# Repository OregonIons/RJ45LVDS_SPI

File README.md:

# RJ45LVDS_SPI

Converts from 4x LVDS over ethernet cable (RJ45) to 4x single-ended digital on a 0.1" header.  
Small footprint board designed to be panel mounted inside a project case.  
Ideal for connecting remote SPI devices to the [Sinara hardware](https://github.com/m-labs/sinara) being designed for [ARTIQ](https://github.com/m-labs/artiq) (specifically the [RJ45_LVDS Kasli module](https://github.com/m-labs/sinara/wiki/EEM_RJ45_LVDS)).  
Voltage translation allows connection to 1.8, 2.5, 3.3, or 5V voltage node logic.

Power
=====

Board requires 3.3V (max current draw is ~200mA). Two options:

1. Apply regulated 3.3V power to the 3.3V pin on either header.  
or
2. Apply unregulated power to UNREG pin and enable the regulator by soldering REG_EN jumper.

- The default regulator is a MIC39100-3.3WS which requires an UNREG input voltage between 3.7 and 16V.  [Datasheet](http://ww1.microchip.com/downloads/en/DeviceDoc/mic39100.pdf)
- When applying unregulated power, the 3.3V pins on the two headers become outputs that can be used to power other things, such as an SPI device. The MIC39100-3.3WS is capable of providing 1A (minus the current required by the board). 
- Adding the optional resistor R5 makes the green LED on the RJ45 jack act as a power indicator.

Channel directions
==================

- Each channel can be independently configured as an input or an output.  
- The channel directions are set via the solder jumpers on the back of the board.  You must set all four directions before powering the board.  
- Each channel has two jumpers which must both be set the same way.

LVDS interface
==============

- Uses Texas Instruments SN65MLVD206 Line Driver and Receiver [Datasheet](http://www.ti.com/lit/ds/symlink/sn65mlvd206.pdf)
- Signalling rates up to 200 Mbps
- Driver has 1.5ns of propagation delay
- Receiver has 4ns of propagation delay

Single-ended digital interface
==============================

- Uses Texas Instruments SN74LVC1T45DBVR Bus Transceiver With Configurable Voltage Translation [Datasheet](http://http://www.ti.com/lit/ds/symlink/sn74lvc1t45.pdf)
- The voltage level of interface must be configured using one of the two V_LOGIC solder jumpers:
1. 3.3V - uses the board’s 3.3V rail
2. EXT - uses voltage supplied at V_LOGIC pin.  Must be in range 1.65-5.5V.
- EXT can be supplied at 'EXT V_LOGIC' pin or the 'UNREG to EXT V_LOGIC' jumper can be used to connect EXT to UNREG.  This would typically be done when powering the board from a regulated +5V supply.
- Propagation delays and data rates depend on V_LOGIC voltage level.  At 3.3V though they are ~4ns and 210Mbps.

RJ45 Connector
==============

Amphenol MRJ-5381-01. See [Datasheet](https://www.amphenolcanada.com/ProductSearch/drawings/AC/MRJ53xxx1.pdf) for panel cutout drawing.

Inverter
========

An optional inverter circuit is provided.  The inverter is an SC70-5 package and is supplied from V_LOGIC.  SN74LVC1GU04 [Datasheet](http://www.ti.com/lit/ds/symlink/sn74lvc1gu04.pdf) is the recommended part as it will work for all supported V_LOGIC voltages (1.8-5V).  Both input and output are wired to a 2-pin 0.1" header  The main envisaged use case is to produce an inverted CS line so that two SPI devices can be driven by the same board.

Release Notes
=============

v0.1 - Initial board fab run.

v0.2 - Second board fab run. Fixed some routing errors that made v0.1 untestable.  Board tested and working.

v0.3 - Changed the RJ45 connector to a right-angled panel-mount version.  Fixed a few silkscreen mistakes.

v0.4 - Fixed a slight error on RJ45 footprint.  Added 3.3V to logic header.  Used nicer solder jumpers.  Added third mounting hole.  Made room so power header could mount on top of board.  Added inverter circuit.

Things to fix in v1.0
=====================

- Inverter input and output labeled wrong on silkscreen.
- Make production files for boardhouse

Licence
=======

Zero-Clause BSD

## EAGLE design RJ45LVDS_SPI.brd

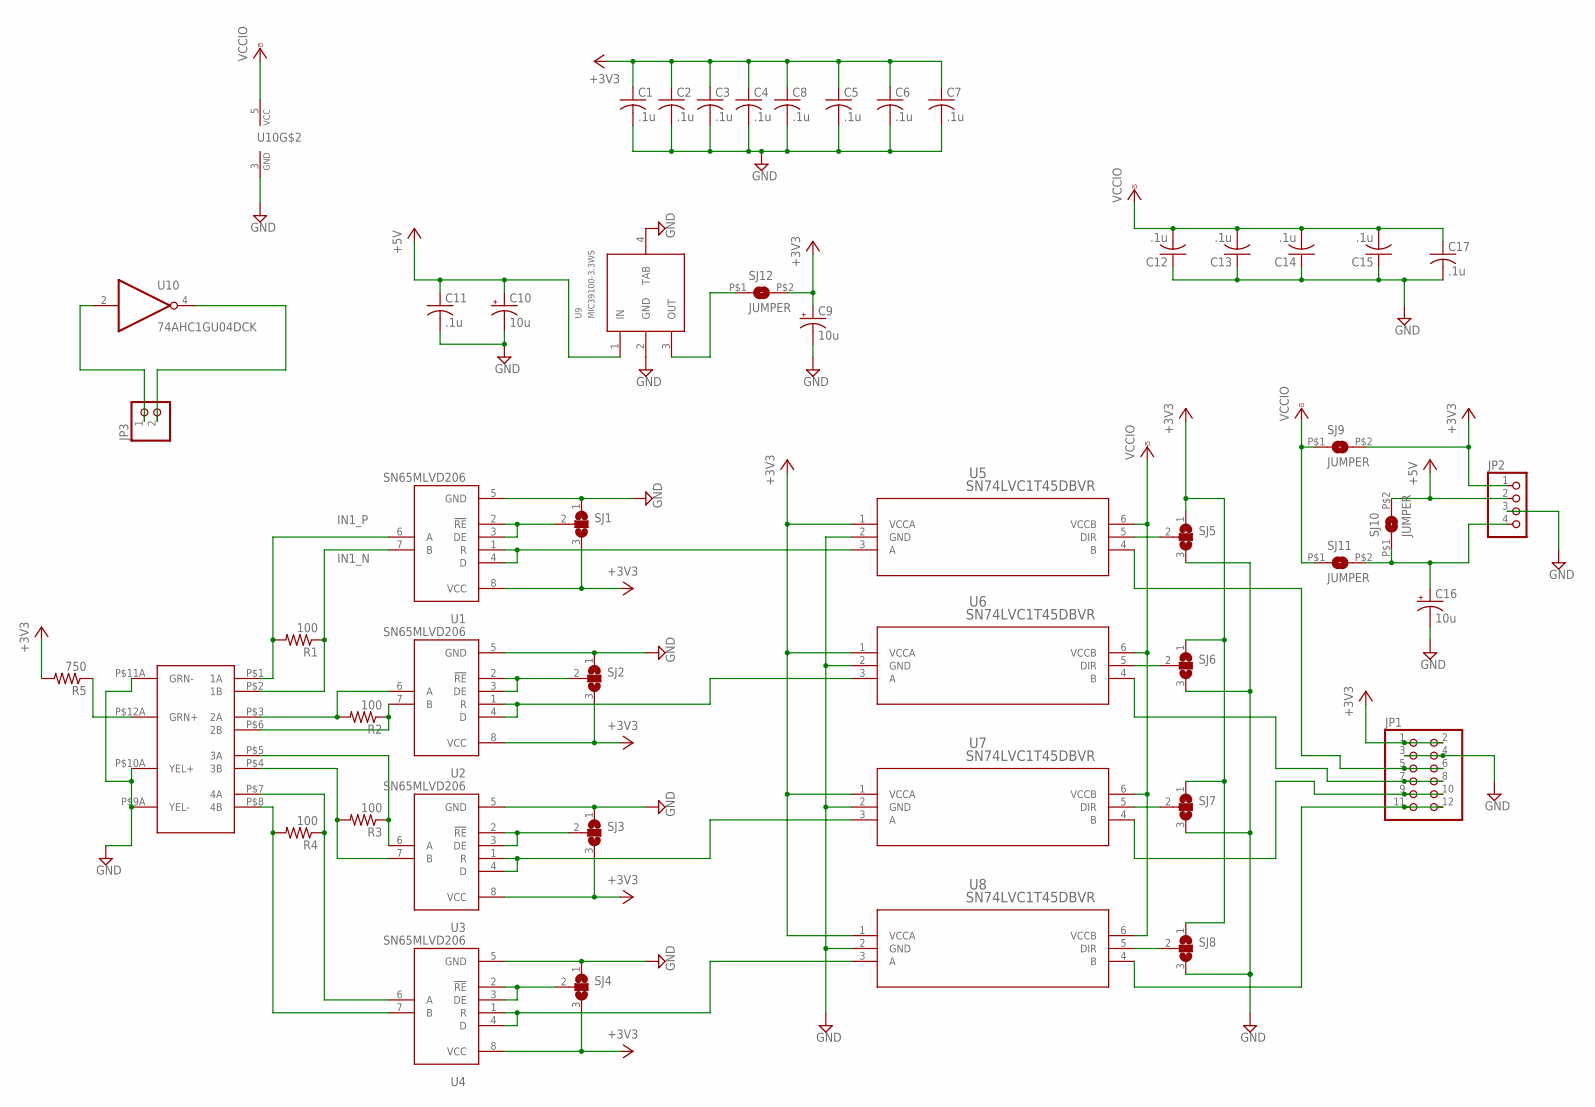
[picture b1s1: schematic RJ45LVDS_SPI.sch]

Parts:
C1, C2, C3, C4, C5, C6, C7, C8, C11, C12, C13, C14, C15, C17: .1u; C0603
C9, C10, C16: 10u; SMC_B
J1: MRJ; MRJ-MEGAMIX
JP1: PINHD-2X6; 2X06
JP2: PINHD-1X4; 1X04
JP3: PINHD-1X2; 1X02
R1, R2, R3, R4: 100; R0603
R5: 750; R0603
SJ1, SJ2, SJ3, SJ4, SJ5, SJ6, SJ7, SJ8: SJ2W; SJ_2
SJ9, SJ10, SJ11, SJ12: JUMPER; 0603JMP
U1, U2, U3, U4: SN65MLVD206; SOIC08-FAIRCHILD
U5, U6, U7, U8: SN74LVC1T45DBVR; DBV6
U9: MIC39100-3.3WS; SOT223
U10: 74AHC1GU04DCK; SC70-5

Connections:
1_33: U1.1 (R), U1.4 (D), U5.3 (A)
2_33: U2.1 (R), U2.4 (D), U6.3 (A)
3_33: U3.1 (R), U3.4 (D), U7.3 (A)
4_33: U4.1 (R), U4.4 (D), U8.3 (A)
+3V3: C1.1, C2.1, C3.1, C4.1, C5.1, C6.1, C7.1, C8.1, C9.+, JP1.1, JP1.2, JP2.1, R5.2, SJ1.3, SJ2.3, SJ3.3, SJ4.3, SJ5.1, SJ6.1, SJ7.1, SJ8.1, SJ9.P$2 (2), SJ12.P$2 (2), U1.8 (VCC), U2.8 (VCC), U3.8 (VCC), U4.8 (VCC), U5.1 (VCCA), U6.1 (VCCA), U7.1 (VCCA), U8.1 (VCCA)
+5V: C10.+, C11.1, JP2.2, SJ10.P$2 (2), U9.1 (IN)
A: JP3.1, U10.2 (I)
GND: C1.2, C2.2, C3.2, C4.2, C5.2, C6.2, C7.2, C8.2, C9.-, C10.-, C11.2, C12.1, C13.1, C14.1, C15.1, C16.-, C17.2, J1.P$9A (YEL-), J1.P$10A (YEL+), J1.P$11A (GRN-), JP1.3, JP1.4, JP2.3, SJ1.1, SJ2.1, SJ3.1, SJ4.1, SJ5.3, SJ6.3, SJ7.3, SJ8.3, U1.5 (GND), U2.5 (GND), U3.5 (GND), U4.5 (GND), U5.2 (GND), U6.2 (GND), U7.2 (GND), U8.2 (GND), U9.2 (GND), U9.4 (TAB), U10.3 (GND)
IN1_N: J1.P$2 (1B), R1.1, U1.7 (B)
IN1_P: J1.P$1 (1A), R1.2, U1.6 (A)
IN2_N: J1.P$6 (2B), R2.1, U2.7 (B)
IN2_P: J1.P$3 (2A), R2.2, U2.6 (A)
IN3_N: J1.P$4 (3B), R3.2, U3.7 (B)
IN3_P: J1.P$5 (3A), R3.1, U3.6 (A)
IN4_N: J1.P$8 (4B), R4.2, U4.7 (B)
IN4_P: J1.P$7 (4A), R4.1, U4.6 (A)
unnamed: SJ3.2, U3.2 (!RE), U3.3 (DE)
unnamed: SJ2.2, U2.2 (!RE), U2.3 (DE)
unnamed: SJ4.2, U4.2 (!RE), U4.3 (DE)
unnamed: SJ1.2, U1.2 (!RE), U1.3 (DE)
unnamed: SJ8.2, U8.5 (DIR)
unnamed: JP1.11, JP1.12, U8.4 (B)
unnamed: SJ5.2, U5.5 (DIR)
unnamed: SJ7.2, U7.5 (DIR)
unnamed: SJ6.2, U6.5 (DIR)
unnamed: JP1.5, JP1.6, U5.4 (B)
unnamed: JP1.7, JP1.8, U6.4 (B)
unnamed: JP1.9, JP1.10, U7.4 (B)
unnamed: C16.+, JP2.4, SJ10.P$1 (1), SJ11.P$2 (2)
unnamed: SJ12.P$1 (1), U9.3 (OUT)
unnamed: J1.P$12A (GRN+), R5.1
NOT_A: JP3.2, U10.4 (O)
VCCIO: C12.2, C13.2, C14.2, C15.2, C17.1, SJ9.P$1 (1), SJ11.P$1 (1), U5.6 (VCCB), U6.6 (VCCB), U7.6 (VCCB), U8.6 (VCCB), U10.5 (VCC)

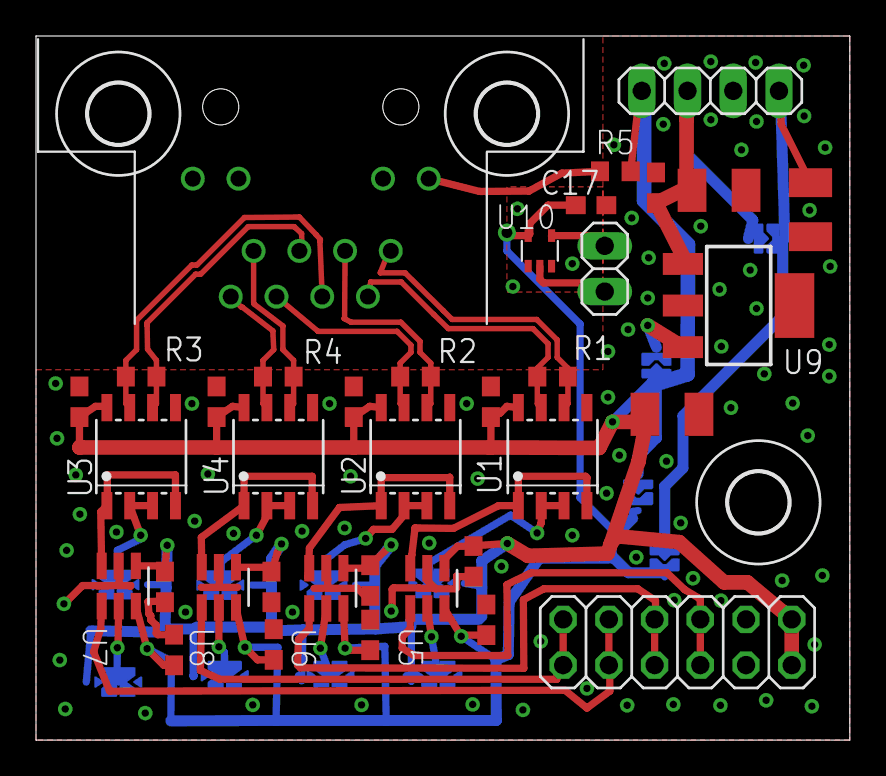
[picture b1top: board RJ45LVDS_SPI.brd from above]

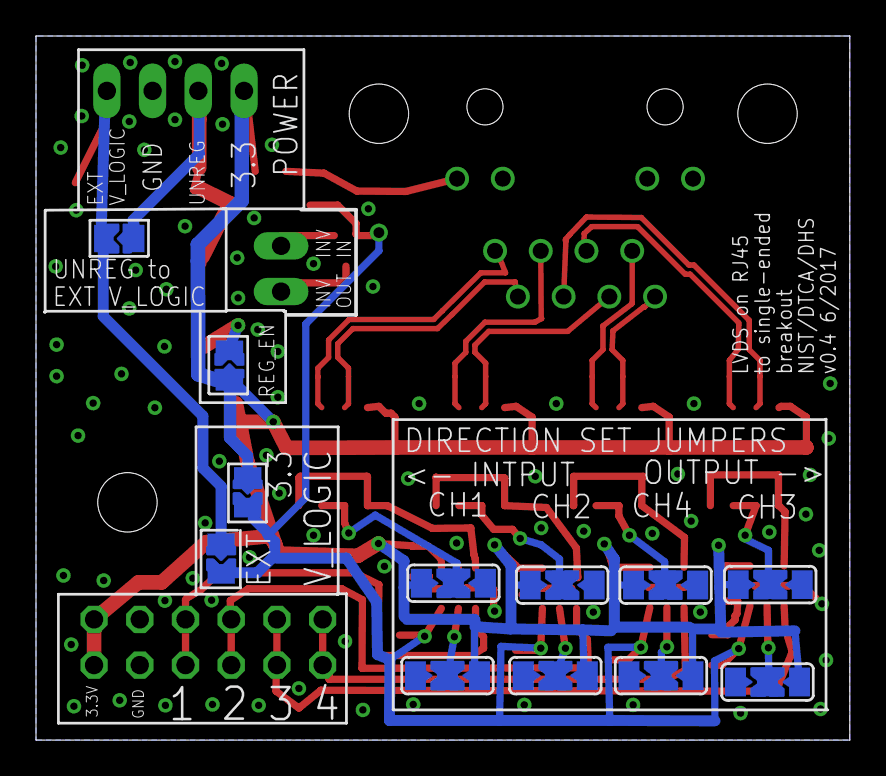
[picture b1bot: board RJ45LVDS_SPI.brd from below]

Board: 2 copper layers, 45.2 x 39.1 mm, 51 parts (12 on the bottom side), 33 nets.

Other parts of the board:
U$1, U$2, U$3: 3,3

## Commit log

2017-04-19 Added boards
2017-04-20 edits
2017-04-21 added level translators
2017-04-21 documentation update
2017-04-21 readme updates
2017-04-21 add gitignore
2017-04-21 deleted backup files
2017-04-21 test gitignore
2017-04-21 fix gitignore
2017-04-21 test
2017-04-21 gahgah
2017-04-21 added pdf
2017-04-22 tweaks
2017-04-22 Bom added
2017-04-25 layout tweaks
2017-04-25 Added mount holes
2017-04-27 fixed labelling on board
2017-04-27 Tidy up and update pdf
2017-04-28 Board tweaks and added gerbers
2017-04-28 fix readme
2017-05-07 Fixed problems with v1.0 board
2017-05-08 added release note to readme
2017-05-08 updated release notes
2017-05-18 Changed RJ45 footprint
2017-05-23 Fixed RJ45 footprint issue
2017-05-23 Updated BOM and pdf
2017-05-23 fixed readme
2017-06-06 v0.4 changes
2022-06-29 Added license
